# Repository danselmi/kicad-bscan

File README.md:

# kicad-bscan – Boundary scan in the KiCad PCB editor

Click a pad in the KiCad PCB editor and see, live, what that pin of the chip is
doing – read through the chip's JTAG boundary-scan register while the board is
running. Watch several pins at once, and for hardware bring-up drive output
pins yourself (EXTEST). The interconnect test checks the connections between
your boundary-scan chips for shorts and opens – what boundary scan was
invented for – and shows faulty nets on the board.

The plugin talks to [OpenOCD](https://openocd.org) (which talks to your JTAG
adapter) and uses the chip's BSDL file to know which bit belongs to which pin.

*The [demo board](demo/README.md), simulated: pads clicked in the PCB editor,
live values in the Pins tab.*

## What it does

- **Live pin values (SAMPLE):** input level and output state (drives 0 / 1 /
  off) of the selected pad, without disturbing the running chip. Snapshots
  taken every 50 ms to 1 s, so static levels and slow signals – not a logic
  analyzer for timing or glitches. Selecting a pin in the schematic works
  too: KiCad's cross-probing selects its pad.
- **Watch list:** keep any number of pins visible, independent of the
  selection. Add the pads selected in KiCad with one click (Ctrl+click selects
  several).
- **Drive pins (EXTEST):** set outputs to 0, 1 or Z from the PCB editor, for
  bring-up and for preparing end-of-line tests. Guarded by a mandatory review
  (see [Driving pins](#driving-pins-extest)).
- **Interconnect test:** finds shorts and opens between the boundary-scan
  pins of your chips in well under a second, net by net; click a faulty net
  to select it in the PCB editor (and, by cross-probing, in the schematic; see
  [Interconnect test](#interconnect-test)).
- **Chip view:** a chip of the chain drawn from its BSDL file, every pin
  coloured by its live state – for large BGAs, and for boards not designed
  in KiCad (see [Chip view](#chip-view)).
- **JTAG chain overview:** every TAP OpenOCD knows, with IR length, assigned
  footprint, BSDL file and package, and a check that the BSDL file matches
  the chip (IR length, IDCODE).
- **Finds BSDL files for you:** point it to your BSDL folders; for each chip it
  offers the files whose IDCODE matches, best-fitting package first.

Settings are stored per project in `<project>.bscan.json` next to the KiCad
project. Without a KiCad project (no board open, or no KiCad at all) they go
to a file of their own: by default `no-project.bscan.json` in the user's
configuration folder (`~/.config/kicad-bscan/` on Linux, `%APPDATA%\kicad-bscan\`
on Windows); **Settings file...** opens another one or saves them as a new
one, e.g. one per board.

## Requirements

- **KiCad 9.0 or 10** with the IPC API enabled (see below).
- **OpenOCD** running with the configuration for your adapter and board. The
  plugin connects to OpenOCD's Tcl port (default `localhost:6666`).
- **BSDL files** for the chips you want to look at (from the chip vendor; for
  FPGAs usually shipped with the vendor tools).
- **Linux or Windows.** Tested on Fedora (KiCad 9) and Windows (KiCad 10).

## Installation

The plugin is built from source.

**1. Dependencies** (Fedora):

```sh
sudo dnf install cmake gcc-c++ protobuf-devel protobuf-compiler nng-devel wxGTK-devel json-devel
```

Needed: a C++23 compiler (GCC ≥ 13), wxWidgets ≥ 3.2, Protobuf, NNG,
nlohmann/json ≥ 3.2.

**Windows:** built with [MSYS2](https://www.msys2.org) in its **UCRT64**
environment (start the "MSYS2 UCRT64" shell):

```sh
pacman -S git mingw-w64-ucrt-x86_64-gcc mingw-w64-ucrt-x86_64-cmake \
          mingw-w64-ucrt-x86_64-ninja mingw-w64-ucrt-x86_64-protobuf \
          mingw-w64-ucrt-x86_64-nng mingw-w64-ucrt-x86_64-wxwidgets3.2-msw \
          mingw-w64-ucrt-x86_64-nlohmann-json
```

The steps below are the same in that shell. MSYS2 also has OpenOCD
(`mingw-w64-ucrt-x86_64-openocd`, without the optional extensions).

**2. Source:** libbsdl is a git submodule. Clone with `--recursive`, or
fetch it in an existing clone (also after a pull that moved it):

```sh
git submodule update --init
```

**3. Build and install:**

```sh
cmake -S . -B build
cmake --build build -j
cmake --install build
```

This installs the plugin into the per-user plugin folder of your KiCad
version, e.g. `~/.local/share/kicad/9.0/plugins/` (Linux) or
`Documents\KiCad\10.0\plugins\` (Windows) – the version is taken from
`kicad-cli version`; the configure step prints the folder it uses. To choose
it yourself: `-DKICAD_VERSION=10.0` or `-DKICAD_PLUGIN_DIR=/path/to/plugins`.
(An existing build folder remembers the folder from its first configure; use
a fresh build folder or add `-U KICAD_PLUGIN_DIR`.)

On Windows the install also copies the DLLs the plugin needs (wxWidgets,
Protobuf, NNG, ...) next to `kicad-bscan.exe`; this needs CMake 3.21 or newer.
If a DLL is not found, the install stops and names it.

On Linux the install also adds a hidden `kicad-bscan.desktop` file and the
window icon to `~/.local/share` – some desktops (GNOME on Wayland in
particular) take the taskbar icon only from there. Not wanted:
`-DBSCAN_INSTALL_DESKTOP_FILE=OFF`.

**4. In KiCad:**

1. *Preferences → Plugins*: enable **"Enable KiCad API"** (off by default).
2. Restart KiCad.
3. The PCB editor now has a **Boundary Scan** button in its toolbar.

## Trying it without hardware

[demo/](demo/README.md) has a small KiCad board with two simulated
boundary-scan chips (a microcontroller and an FPGA) and a JTAG simulator for
OpenOCD: pins, EXTEST and the interconnect test work as with a real board.

## Getting started

1. **Start OpenOCD** with your usual configuration, e.g.
   `openocd -f interface/... -f board/...`. The plugin uses OpenOCD's Tcl
   port, which is on by default (port 6666). If your configuration contains
   `tcl_port disabled`, remove that line; if it uses another port, set it in
   the plugin with **Address...**.
2. **Open the board** in the PCB editor and click **Boundary Scan**. The window
   stays open while you work; *pin* (top right) keeps it on top.
   The window has three tabs: **JTAG chain** (setup), **Pins** (live
   values) and **Interconnect test**; the connection lines and the red
   EXTEST bar above them are always visible.
3. **JTAG chain** tab: the table lists the TAPs OpenOCD found. For each chip
   you want to use:
   - **Reference:** type the reference designator (e.g. `U1`), or select the
     footprint in KiCad and click **←**.
   - **BSDL file:** click **...** and choose the file. If you have set up BSDL
     folders and matching files were found, the empty field says so and
     **...** lists them first.
   - **Pin map:** the package, if the BSDL file describes several.
   - **Check** shows whether the BSDL file matches the chip.

   Settings of a TAP that is no longer in OpenOCD's chain stay in the table
   (grey, "not in chain"), e.g. while OpenOCD runs with another
   configuration; **Forget...** in that row removes them.
4. **Pins** tab: **click a pad** of that footprint in KiCad. *Selected pad*
   shows its net, the chip port, and the live input and output values.
5. **Watch list:** select pads in KiCad and click **+ Selection** to keep them
   on the list.

One pin is selected everywhere: selecting rows in the watch list selects
their pads in KiCad and highlights the pin in the chip view; selecting a pad
in KiCad (or a pin in the chip view) selects its row in the watch list, if
it is on the list.

The line at the top of the Pins tab shows what is being sampled and lets you
set the sampling interval. The values are for looking at, not for timing
measurements: depending on the adapter, a few to a few tens of samples per
second are possible.

## Chip view

**Chip view...** (top right) opens a separate window that draws one chip of
the chain with the live state of all its pins: drives 1 / 0, reads 1 / 0
(output off), toggling (drawn half 1, half 0), not sampled; JTAG, power and
pins without boundary-scan cells in their own colours (legend below the
drawing). Choose
the chip at the top; it needs a BSDL file and a reference (JTAG chain tab).

- **Layout:** BSDL files describe pins, not the package, so the layout is
  guessed from the pin names: ball names (A1, AB12) give a BGA grid, numbers
  a quad package with the pins spread evenly over four sides, pin 1 top left,
  counter-clockwise. If that is wrong, set the layout: BGA, quad (optionally
  with the pins per side, e.g. `30,20,30,20` for left, bottom, right, top) or
  dual (SOIC, TSSOP). It is saved per chip.
- **Click a pin:** it becomes the selected pad in the Pins tab (until you
  select something else in KiCad), is selected on the board if the board has
  it, and in the watch list if it is on it. **Ctrl+click** selects several
  pins. Pins selected elsewhere are highlighted if they belong to the chip
  shown (the view does not switch chips by itself). **Right-click:** add the
  selected pins to the watch list, or drive them (EXTEST, with the usual setup
  and review).
- **Without a board** (chip not on the open KiCad board, or no KiCad at all)
  the window says so in red: the plugin cannot know what the pins are
  connected to, so the EXTEST review cannot point out pins on nets either.
  Check the board yourself before you drive pins.

**Without KiCad:** start the plugin directly – it is an ordinary program in
the plugin folder the install step printed, e.g.
`~/.local/share/kicad/9.0/plugins/com.github.danselmi.kicad-bscan/kicad-bscan`
(Linux) or `Documents\KiCad\10.0\plugins\com.github.danselmi.kicad-bscan\kicad-bscan.exe`
(Windows). The KiCad line then says "not connected"; the JTAG chain tab, the
Pins tab and the chip view work as usual (a reference is still needed per
chip: any name), and the settings go to a file of their own (see above).

## Finding BSDL files

**BSDL folders...** (JTAG chain tab, below the table) sets where to look; subfolders
are included (`*.bsd`, `*.bsdl`, `*.bsm`):

- **Your folders** apply to all projects – e.g. your collection of vendor BSDL
  files.
- **Project folders** are stored in the project file – e.g. the folder your
  FPGA tool writes its BSDL file to. Files from there are listed first.

For a chip without a (matching) BSDL file, the plugin offers the files whose
IDCODE and IR length match – one entry per file and package, best fitting
first ("Pads found": how many of the footprint's pads exist in the package).
Nothing is assigned automatically; you always choose.

The first search through a large collection takes a while (e.g. 20 s);
afterwards results come from a cache and files are only read again when they
change. Choosing the same BSDL file again re-reads it – handy when your FPGA
tool regenerated it.

## Driving pins (EXTEST)

> **Warning.** In EXTEST the boundary-scan register drives **all** pins of the
> chip, and the chip's own logic is disconnected from them. A wrong level can
> damage your hardware – think of a pin that drives a power stage, a bridge or
> an LED that is only meant to be pulsed. An FPGA may also lose its clock.
> Use EXTEST for bring-up and test preparation, not on a board doing its job.

**Starting EXTEST** – click **EXTEST...** in the chip's row, or one of the
**0 / 1 / Z** buttons of a pin (selected pad or watch list):

1. **Setup:** choose the state every output pin gets when EXTEST starts:
   *safe (BSDL)* (the vendor's safe value, default), *Z* (off), *0*, *1*, or
   *keep* (what the chip drives right now; only for static levels). The list
   shows the net of each pin; the settings are saved for next time. Filters
   help with large chips: only pins with a net, only pins that change when
   EXTEST starts, and a search for pin, port or net.
2. **Review:** every pin that changes its state is listed. Pins that are
   connected on your board but left at the BSDL default are marked red.
   Conflicts (e.g. pins sharing an output enable that need different states)
   block activation. You confirm with a checkbox before anything is driven.

**While EXTEST is active** a red bar at the top says so and offers **Leave
EXTEST**. Drive pins with the **0 / 1 / Z** buttons of the selected pad, or
**Drive selected** (or right-click) in the watch list; driven pins are marked
with ▶. Changing a pin that shares its output enable with others asks first.

**Safety rules built in:**

- If the connection to OpenOCD is lost, EXTEST is left as soon as it is back,
  and never resumed automatically.
- Closing the window asks whether to return the chips to normal operation.
- If you keep EXTEST when closing, the next session does not touch that chip
  until you decide: **Leave EXTEST**, or **Take over...** (only with an
  OpenOCD that has `jtag cur_ir`, see below) to continue driving the same
  states – or a new plan – without the pins returning to the chip's logic in
  between. Several chips kept in EXTEST are taken over together (needs
  `jtag scan` as well); you choose the states for each in turn.

**Keep OpenOCD quiet while in EXTEST.** Anything else using the JTAG chain
can interrupt EXTEST: OpenOCD's background polling of targets in the same chain
(`poll off` stops it), or an IPDBG server. Each interruption hands the pins
back to the chip's logic for a moment.

- The review warns if background polling is on.
- With an OpenOCD that has `jtag cur_ir` (see below), interruptions are
  detected: EXTEST and your pin states are restored at once, and the red bar
  keeps a warning with the count and time of the last one. A board reset that
  OpenOCD does not see (e.g. a reset button) is not detected, but the next
  scan restores EXTEST all the same.

## Interconnect test

The **Interconnect test** tab checks the soldering between the chips with
BSDL files: every net that connects at least two of their boundary-scan pins
is driven by one pin with a sequence of test patterns while the other pins
listen. A net that reads another net's values is shorted to it; a pin that
does not see its net is open.

*The demo board with a simulated short (D3–D4) and an open (U2 pin 5):
the selected net D2 is highlighted in the PCB editor.*

- **The list** shows every net with a boundary-scan pin, in groups: tested,
  fixed (kept out by starting states), other parts on the net, and not
  testable (only one boundary-scan pin, no pin that can drive, or an output
  enable shared with a pin that would then drive). Before the first run the
  nets to test show "will be tested", afterwards their result.
- **Nets with other parts** (resistors, connectors, other ICs) are not tested
  by default: the test would drive those parts too. Right-click (or
  double-click) such a net to include it after checking what is connected.
- **Starting states are constraints:** a pin with a starting state (EXTEST
  setup) keeps it during the test; its net is not tested. On a chip that is
  already in EXTEST, a pin you set by hand (drive buttons) keeps its state
  the same way. Right-click a fixed net to test it (after a question: its
  starting states are removed, pins set by hand get test patterns and their
  state back afterwards) or to edit the starting states. The EXTEST setup
  dialog shows the same while you edit: its column "Interconnect test" says
  per pin whether its net is tested, and marks the starting states that keep
  a net out.
- **Review:** above **Run** the tab says how many nets are driven, which chips
  go into EXTEST for the test and which nets with other parts are driven;
  tick the checkbox to confirm. Chips enter EXTEST only for the test and
  return to normal operation afterwards; chips already in EXTEST drive what
  they drove before.
- **Run** applies the patterns once; **Repeat** again and again until
  **Stop**, counting faults per net – press on parts or bend the board to
  find intermittent joints. A net that failed stays red; "now OK" shows that
  it passes in the latest run. The next Run or Repeat starts the counters
  from zero.
- **Results:** OK, "short with NET_X", "open at U3 pin 12", or "all receivers
  read 0/1" (open at the driving pin, or a short to GND / a supply). Click a
  net to select it in the PCB editor.

A test that involves several chips needs an OpenOCD with `jtag scan` (see
below); with a standard OpenOCD it runs only if all tested nets connect
pins of one chip.

## Optional OpenOCD extensions

The plugin works with a standard OpenOCD. Two additions make it better and
are used automatically when available (not yet in upstream OpenOCD):

- **`jtag cur_ir <tap>`** ([change 9947](https://review.openocd.org/c/openocd/+/9947)) –
  the instruction OpenOCD last loaded into a TAP. With it, the plugin knows
  whether a chip is really in EXTEST (instead of "probably"), notices EXTEST
  set by other programs, offers *Take over*, and detects interruptions of
  EXTEST.
- **`jtag scan`** ([change 9948](https://review.openocd.org/c/openocd/+/9948)) –
  instruction and data scan as one operation, so nothing else (target
  polling, IPDBG) can change the instruction in between. It scans several
  chips at once, so with it **several chips can be in EXTEST** at the same
  time (e.g. to test the connections between them), and the other chips keep
  being sampled meanwhile.

Both are in review for upstream OpenOCD. To use them now, build OpenOCD with
the two changes applied (each change page offers its patch under
*Download*). Whether your OpenOCD has them: `help jtag` in OpenOCD's console
(telnet port 4444) lists them.

## Troubleshooting

- **No "Boundary Scan" button:** check that the KiCad API is enabled and KiCad
  was restarted after installing; the plugin must be in the plugin folder of
  your KiCad version (`9.0` or `10.0`, see the configure output). KiCad skips
  plugins it cannot load without a message; start it with
  `KICAD_ENABLE_WXTRACE=1 WXTRACE=KICAD_API kicad` to see why.
- **"OpenOCD: not connected":** OpenOCD is not running, its Tcl port is
  disabled (`tcl_port disabled` in the configuration), or it listens on
  another address or port – use **Address...**.
- **Check says the BSDL file does not match:** IR length or IDCODE differ –
  usually a different chip or package revision; the details below the table
  say what differs.
- **Values of a pin show "–":** the pin has no boundary-scan cell for that
  direction (e.g. an input-only pin has no output state).

## Known limitations

- Without `jtag scan` (see above) only one chip at a time can be in EXTEST,
  and while it is, the other chips in the chain are not sampled (their pins
  show "paused"): OpenOCD puts all other chips into BYPASS for every scan,
  which would end EXTEST.
- EXTEST does not mix with other JTAG activity on the chain (target polling,
  IPDBG): it is interrupted, restored and reported (see above).
- "Stay on top" is ignored by some Wayland desktops (GNOME in particular);
  starting KiCad with `GDK_BACKEND=x11` helps.
- Windows: no ready-made package yet.

## License

GPL-3.0-only, see [LICENSE](LICENSE). Included third-party code keeps its
license: libbsdl (MPL-2.0, submodule `third_party/libbsdl/`) and the KiCad API `.proto`
files (GPL-3.0-or-later, `third_party/kicad-api/`).

## Feedback

Problems, questions and ideas: please open an issue in this repository's
issue tracker; pull requests are even better. Ideas already collected are in
[doc/TODO.md](doc/TODO.md) ("Ideas").

## For developers

Build options, tests without hardware (JTAG simulator, fake KiCad server) and
design notes: [doc/DEVELOPMENT.md](doc/DEVELOPMENT.md). Open points:
[doc/TODO.md](doc/TODO.md).

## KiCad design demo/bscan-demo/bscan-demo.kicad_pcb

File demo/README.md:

# Demo board

A small board with two boundary-scan chips, simulated on a JTAG chain, to try
the plugin without hardware (and to take screenshots).

- **U1** – a microcontroller, *BSDEMO_M32* (QFN-32): data bus, control
  lines, IRQ, I2C, and GPIOs, a button and a status LED on connector J1.
- **U2** – an FPGA, *BSDEMO_F48* (TQFP-48): the other end of the bus, four
  LEDs and an SPI connector J2.

Both chips are fictional; their BSDL files are in `bscan-demo/bsdl/`. The
JTAG chain is TDI → U1 → U2 → TDO.

## Running it

You need Python 3 and OpenOCD; KiCad 9 or newer with the plugin installed.

```sh
python3 demo/demo_sim.py &
openocd -f demo/openocd-demo.cfg
```

Then open `demo/bscan-demo/bscan-demo.kicad_pro` in KiCad, open the PCB and
click **Boundary Scan**. The project's settings (`bscan-demo.bscan.json`)
already assign the TAPs to U1 and U2 with their BSDL files and fill the watch
list.

While the chips are not in EXTEST, their own logic is running: U1 counts on
the data bus (D0–D7), drives a clock (CLK) and blinks STAT; U2 counts on its
LEDs and toggles PWM0/PWM1. The button on J1 (BTN) is pressed for half a
second every four seconds. Click pads to see them.

## Things to try

- **Pins tab:** click pads of U1 and U2 in the PCB editor, add some to the
  watch list.
- **Drive pins:** click an LED pad of U2 (pins 26–29) and use the
  **0 / 1 / Z** buttons, or **Drive selected** (or right-click) in the watch
  list; U2 goes into EXTEST (setup and review first).
- **Interconnect test:** 13 nets are tested (D0–D7, nCS, nRD, nWR, CLK, IRQ).
  The others show why they are not:
  - *nPROG* – fixed by the starting state of U1 pin 11 ("1", set in the
    project so the FPGA stays configured);
  - *PWM0* – its driver U2 pin 47 shares the output enable with pin 30
    (PWM1);
  - *SDA*, *SCL* – other parts on the net (the pull-up resistors R7, R8);
    include them to test them anyway;
  - the LEDs, J1 and J2 – only one boundary-scan pin.
- **Faults:** start the simulator with faults and run the test again:

  ```sh
  python3 demo/demo_sim.py --short D3,D4 --open U2.5
  ```

  `--short NET1,NET2` shorts two nets, `--open REF.PIN` leaves a pin
  unsoldered; both can be repeated. Restart OpenOCD after restarting the
  simulator.

Testing both chips together needs OpenOCD with `jtag scan` (see
[Optional OpenOCD extensions](../README.md#optional-openocd-extensions)).
With a standard OpenOCD only one chip can be in EXTEST at a time, so the
interconnect test between U1 and U2 cannot run; the plugin says so.

## Files

Everything except the two scripts is generated by `generate.py` from one
description of the board (chips, pins, nets, placement, tracks); run it
after changing that description:

```sh
python3 demo/generate.py
```

| File | |
|---|---|
| `generate.py` | the board description and the generator |
| `demo_sim.py` | the JTAG simulator (OpenOCD `remote_bitbang`, port 5555) |
| `openocd-demo.cfg` | OpenOCD configuration for the simulator |
| `bscan-demo/` | the KiCad project (board only, no schematic) with the BSDL files and the plugin's settings |
| `sim/board.json` | chips, boundary registers and nets for the simulator |

The plugin saves its settings to `bscan-demo/bscan-demo.bscan.json` as you
work; `git checkout demo/bscan-demo` restores the original ones.

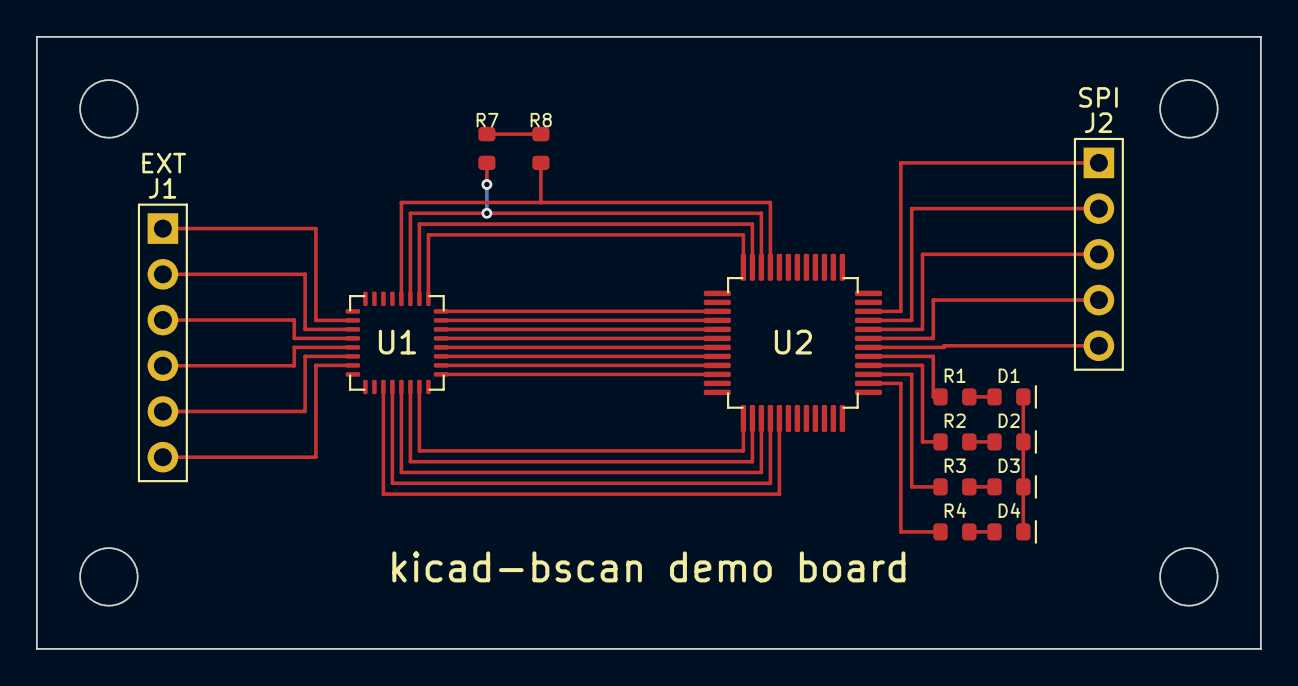
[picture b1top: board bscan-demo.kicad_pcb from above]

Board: 2 copper layers, 68.0 x 34.0 mm, 14 parts (0 on the bottom side), 38 nets.

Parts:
D1, D2, D3, D4: LED; LED_0603_1608Metric
J1: EXT; PinHeader_1x06_P2.54mm
J2: SPI; PinHeader_1x05_P2.54mm
R1, R2, R3, R4: 330; R_0603_1608Metric
R7, R8: 4k7; R_0603_1608Metric
U1: BSDEMO_M32; QFN-32_5x5mm_P0.5mm
U2: BSDEMO_F48; TQFP-48_7x7mm_P0.5mm

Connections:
+3V3: R7.2, R8.2
AUX0: J2.1, U2.34
BTN: J1.5, U1.6
CLK: U1.12, U2.16
D0: U1.24, U2.3
D1: U1.23, U2.4
D2: U1.22, U2.5
D3: U1.21, U2.6
D4: U1.20, U2.7
D5: U1.19, U2.8
D6: U1.18, U2.9
D7: U1.17, U2.10
GND: D1.1, D2.1, D3.1, D4.1
GPIO0: J1.2, U1.3
GPIO1: J1.3, U1.4
GPIO2: J1.4, U1.5
IRQ: U1.25, U2.48
LED1: R1.1, U2.29
LED1_A: D1.2, R1.2
LED2: R2.1, U2.28
LED2_A: D2.2, R2.2
LED3: R3.1, U2.27
LED3_A: D3.2, R3.2
LED4: R4.1, U2.26
LED4_A: D4.2, R4.2
PWM0: U1.26, U2.47
PWM1: J2.5, U2.30
SCL: R8.1, U1.28, U2.45
SDA: R7.1, U1.27, U2.46
SPI_MISO: J2.2, U2.33
SPI_MOSI: J2.3, U2.32
SPI_SCK: J2.4, U2.31
STAT: J1.6, U1.7
nCS: U1.15, U2.13
nPROG: U1.11, U2.17
nRD: U1.14, U2.14
nRESET: J1.1, U1.2
nWR: U1.13, U2.15

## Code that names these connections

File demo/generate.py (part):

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        # bottom side, left to right: control lines to the FPGA
        9: ("TCK", "tap", None),
        10: ("TMS", "tap", None),
        11: ("PB4", O3, ["drive", 1]),  # nPROG: keep the FPGA configured
        12: ("PB3", O2, ["toggle", 0.5]),  # CLK
        13: ("PB2", O3, ["drive", 1]),  # nWR
        14: ("PB1", O3, ["drive", 1]),  # nRD
        15: ("PB0", O3, ["drive", 1]),  # nCS
        16: ("VDD", "linkage", None),
        # right side, bottom to top: data bus D7 .. D0
        17: ("PA7", IO, ["counter", 7, 0.25]),
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# J1: reset, GPIOs, button and status LED
for pin, name, header in (
    (2, "nRESET", 1),
    (3, "GPIO0", 2),
    (4, "GPIO1", 3),
    (5, "GPIO2", 4),
    (6, "BTN", 5),
    (7, "STAT", 6),
):
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

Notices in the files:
demo/generate.py:
SPDX-License-Identifier: GPL-3.0-only
